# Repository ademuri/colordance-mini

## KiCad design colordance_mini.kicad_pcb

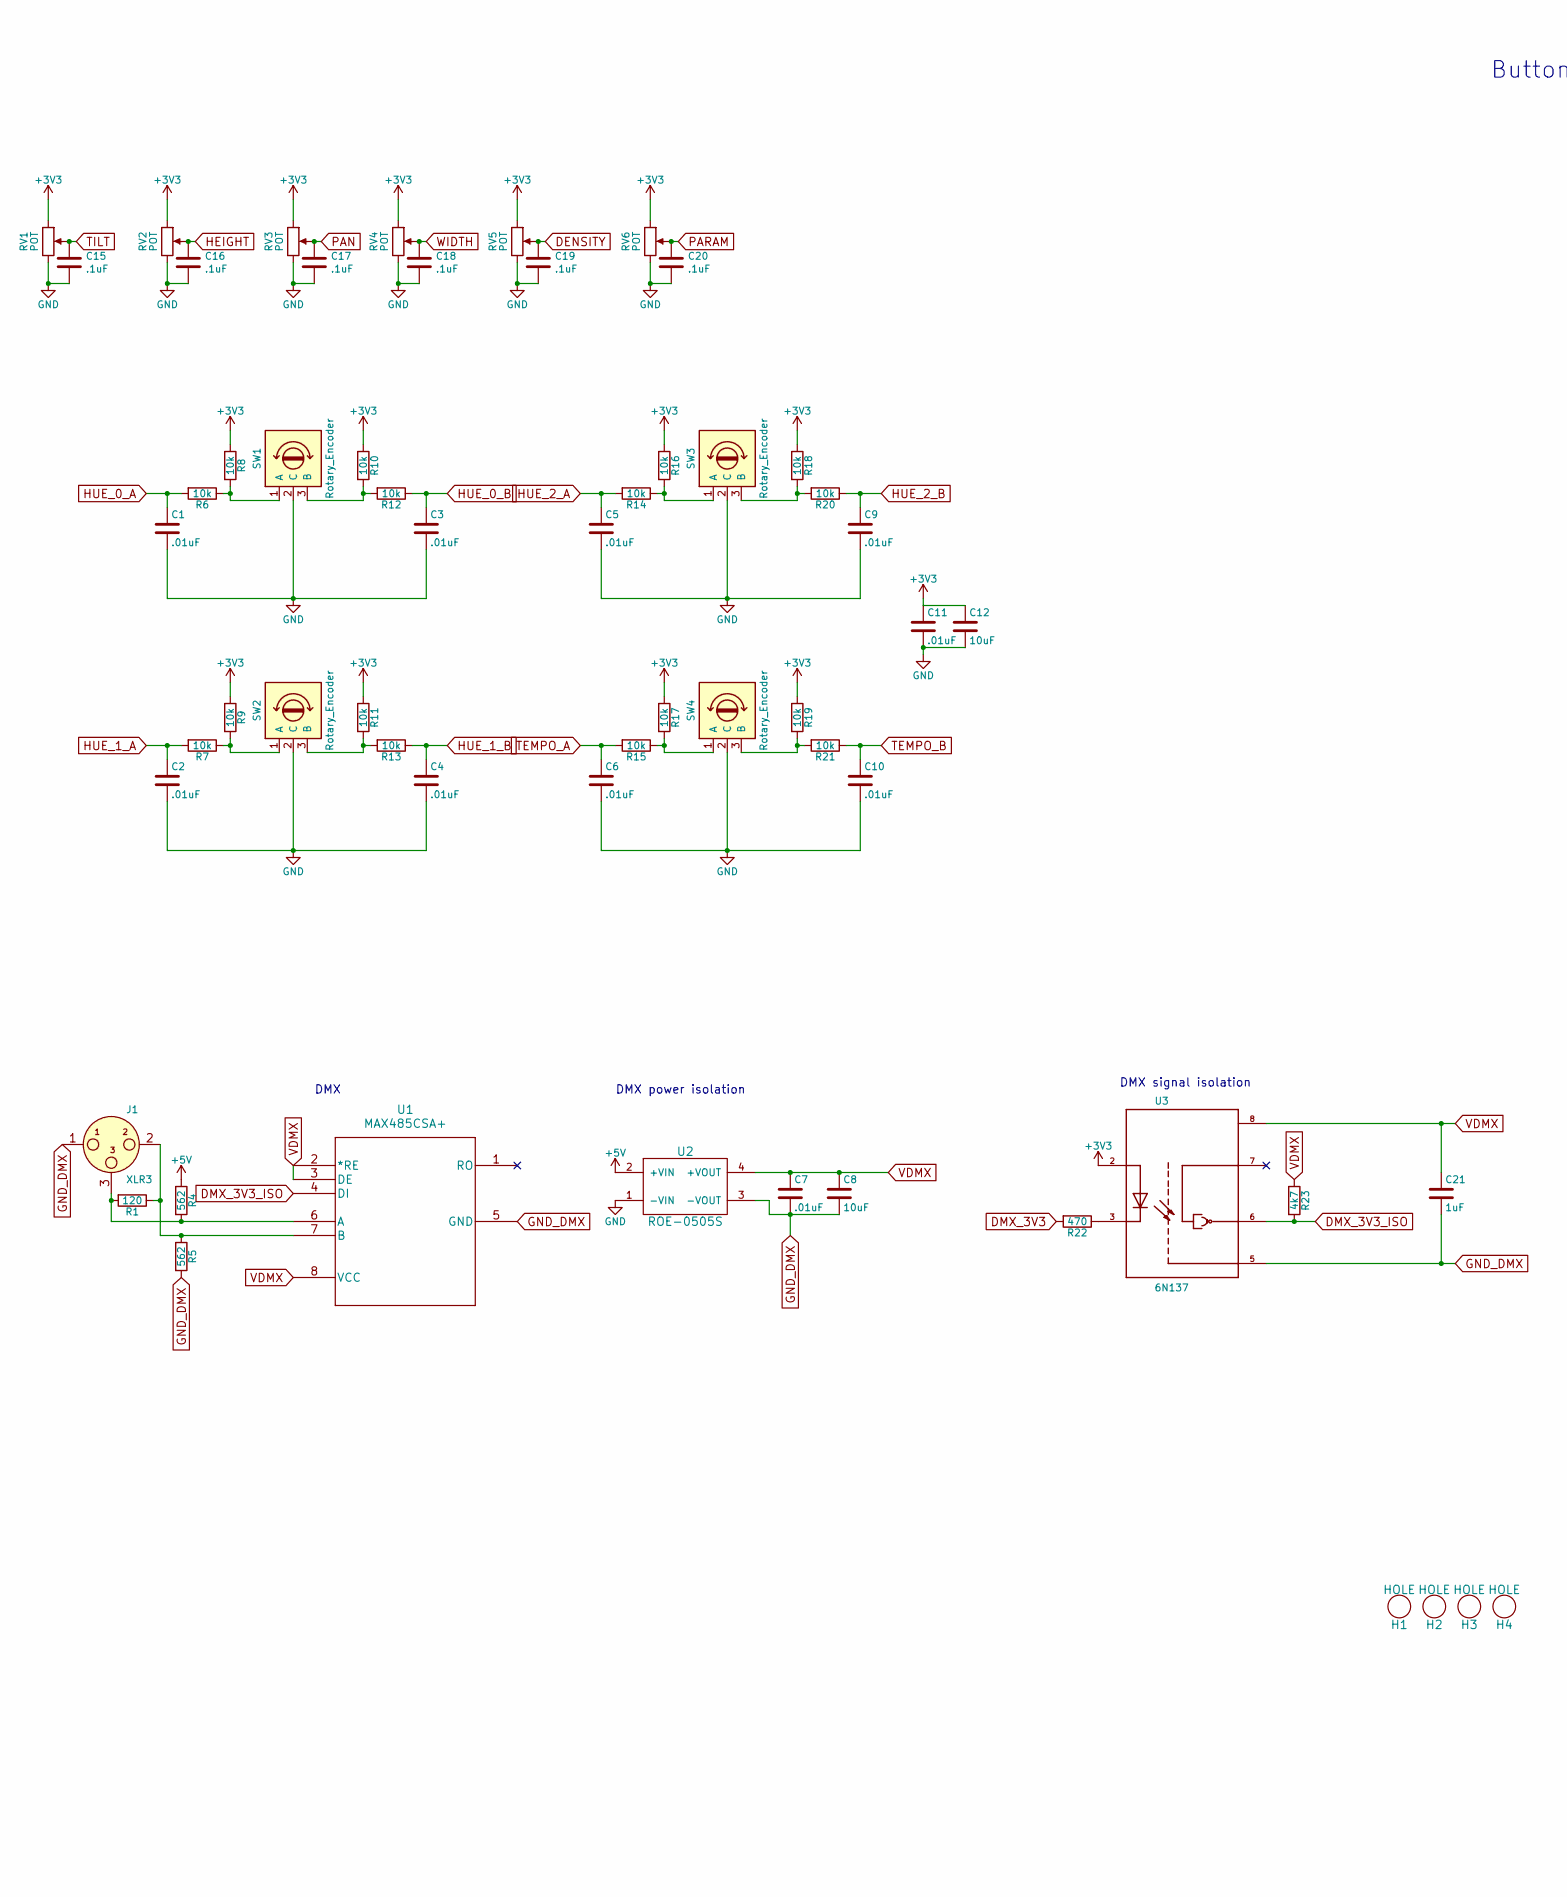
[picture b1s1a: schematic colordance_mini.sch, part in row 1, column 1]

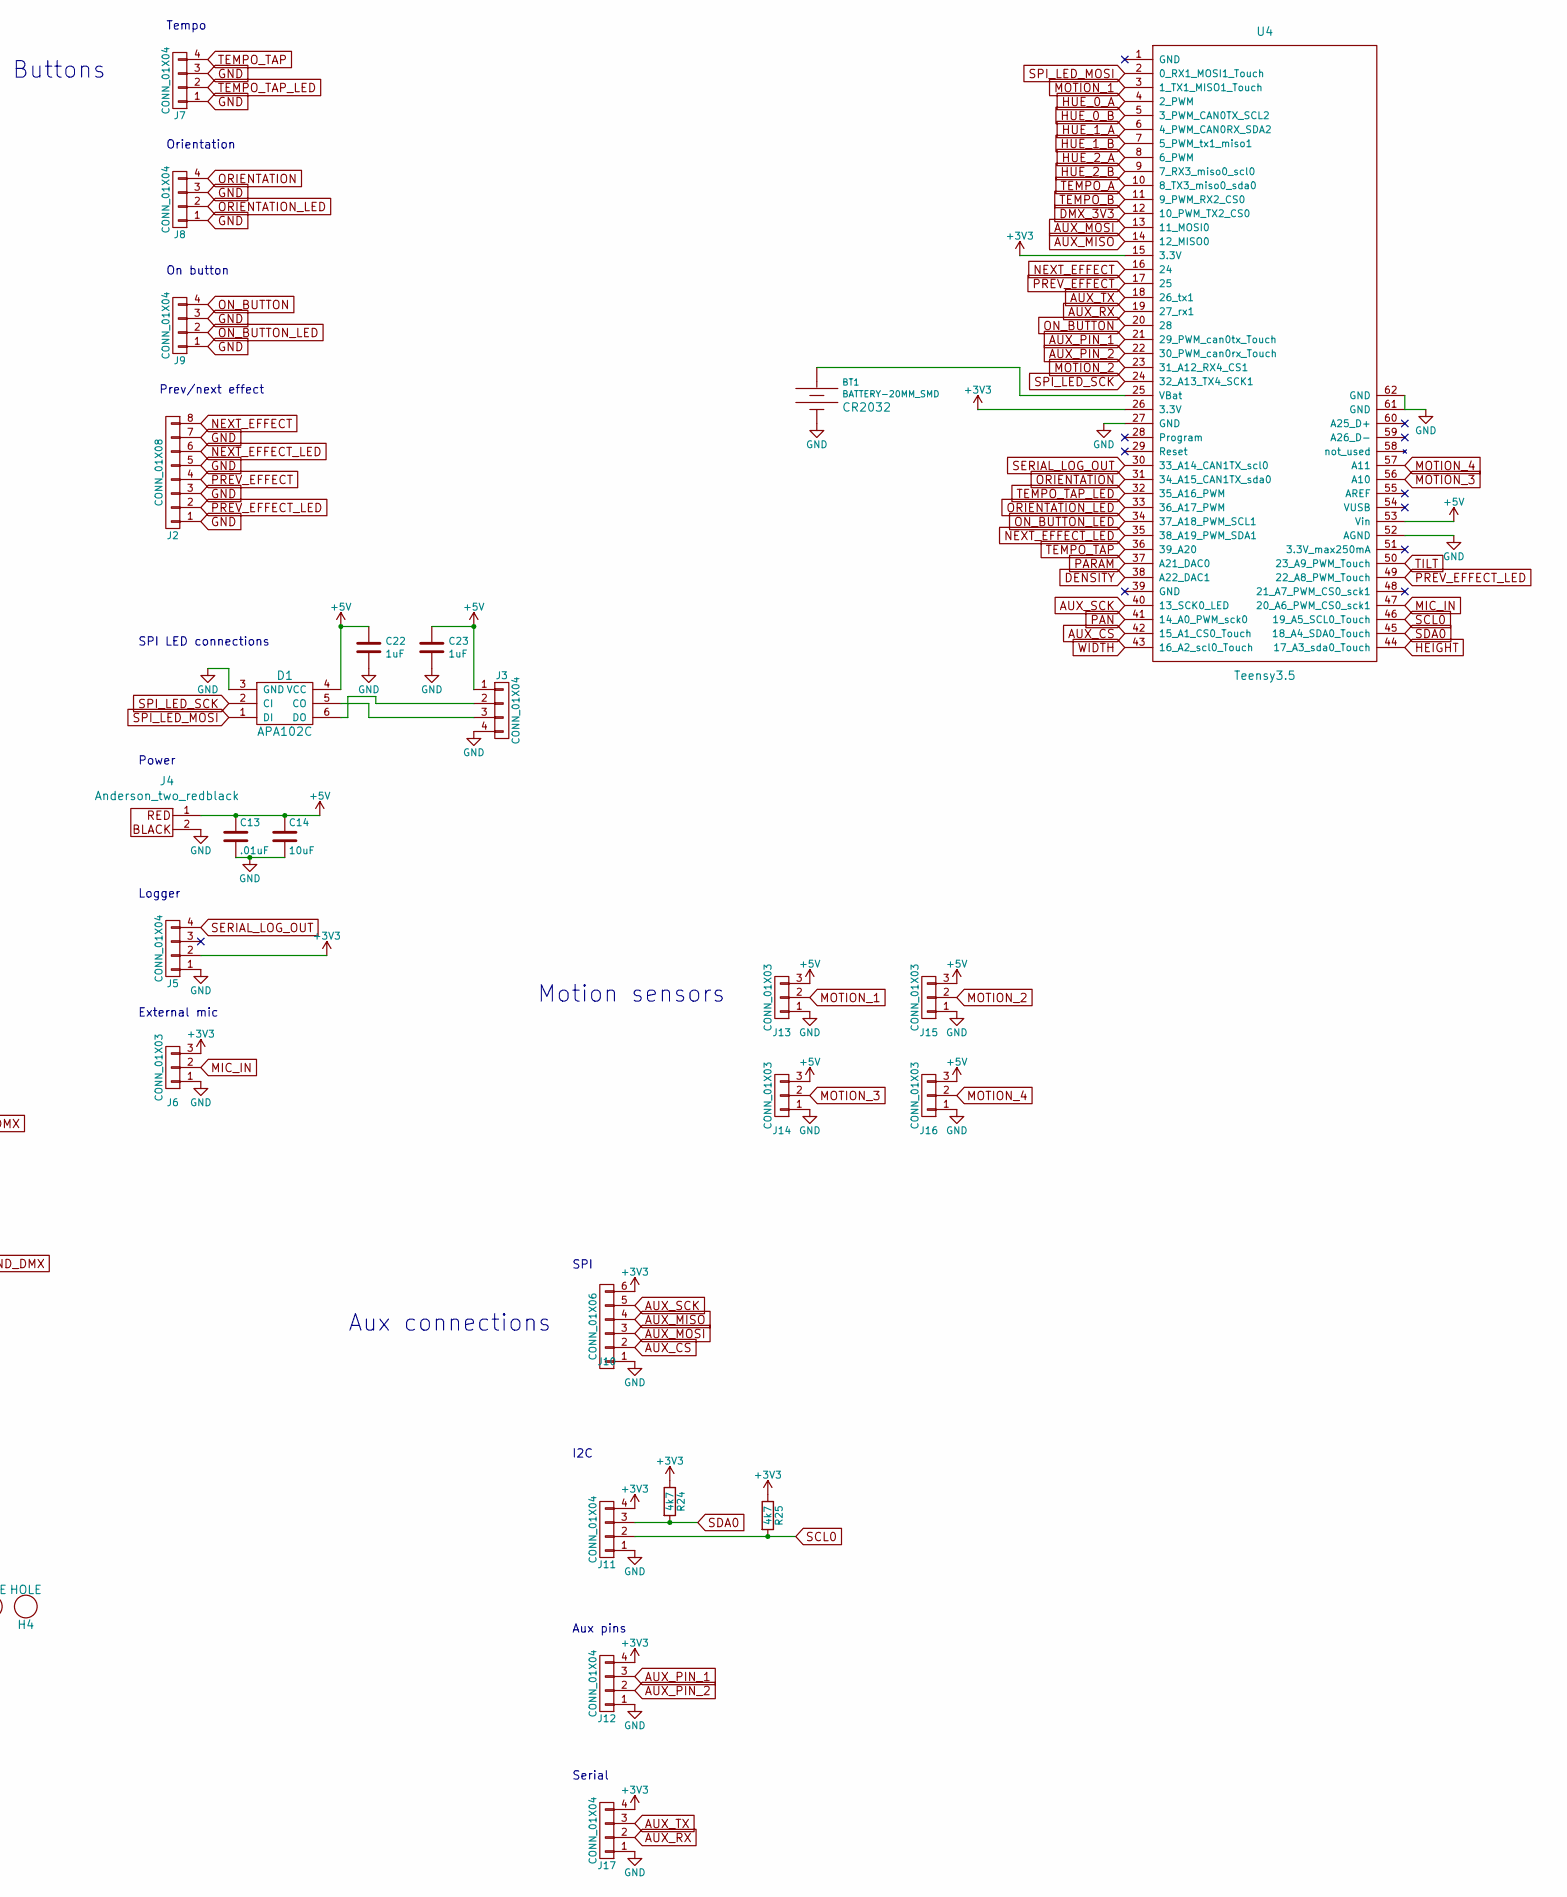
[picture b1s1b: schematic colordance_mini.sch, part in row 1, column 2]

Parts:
BT1: BATTERY-20MM_SMD; BATTCON_20MM
C1, C2, C3, C4, C5, C6, C7, C9, C10, C11, C13: .01uF; C_0603_HandSoldering
C8, C12, C14: 10uF; C_0603_HandSoldering
C15, C16, C17, C18, C19, C20: .1uF; C_0603_1608Metric_Pad1.05x0.95mm_HandSolder
C21, C22, C23: 1uF; C_0603_1608Metric_Pad1.05x0.95mm_HandSolder
D1: APA102C
H1, H2, H3, H4: HOLE; HOLE_M4
J1: XLR3; NC3FAH
J2: CONN_01X08; 1985250_phoenix_8pos_3.5mm
J3: CONN_01X04; PinHeader_1x04_P2.54mm_Vertical
J4: Anderson_two_redblack; Anderson_1337G3_straight_two
J5, J11, J12, J17: CONN_01X04; Pin_Header_Straight_1x04_Pitch2.54mm
J6, J13, J14, J15, J16: CONN_01X03; Pin_Header_Straight_1x03_Pitch2.54mm
J7, J8, J9: CONN_01X04; 1985218_phoenix_4pos_3.5mm
J10: CONN_01X06; Pin_Header_Straight_1x06_Pitch2.54mm
R1: 120; R_0603_HandSoldering
R4, R5: 562; R_0603_HandSoldering
R6, R7, R8, R9, R10, R11, R12, R13, R14, R15, R16, R17, R18, R19, R20, R21: 10k; R_0603_HandSoldering
R22: 470; R_0603_HandSoldering
R23, R24, R25: 4k7; R_0603_HandSoldering
RV1, RV2, RV3, RV4, RV5, RV6: POT; BOURNS_SLIDE_POT_45MM
SW1, SW2, SW3, SW4: Rotary_Encoder; BOURNS_PEC11R_ENCODER
U1: MAX485CSA+; SOIC-8-N
U2: ROE-0505S
U3: 6N137; DIP762W50P254L977H451Q8
U4: Teensy3.5; Teensy35_36

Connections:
+3V3: C11.1, C12.1, J5.2, J6.3, J10.6, J11.4, J12.4, J17.4, R8.1, R9.1, R10.1, R11.1, R16.1, R17.1, R18.1, R19.1, R24.1, R25.1, RV1.1, RV2.1, RV3.1, RV4.1, RV5.1, RV6.1, U3.2 (A), U4.15 (3.3V), U4.26 (3.3V)
+5V: C13.1, C14.1, C22.1, C23.1, D1.4 (VCC), J3.1, J4.1, J13.3, J14.3, J15.3, J16.3, R4.1, U2.2 (+VIN), U4.53 (Vin)
AUX_CS: J10.2, U4.42 (15_A1_CS0_Touch)
AUX_MISO: J10.4, U4.14 (12_MISO0)
AUX_MOSI: J10.3, U4.13 (11_MOSI0)
AUX_PIN_1: J12.3, U4.21 (29_PWM_can0tx_Touch)
AUX_PIN_2: J12.2, U4.22 (30_PWM_can0rx_Touch)
AUX_RX: J17.2, U4.19 (27_rx1)
AUX_SCK: J10.5, U4.40 (13_SCK0_LED)
AUX_TX: J17.3, U4.18 (26_tx1)
DENSITY: C19.1, RV5.2, U4.38 (A22_DAC1)
DMX_3V3: R22.2, U4.12 (10_PWM_TX2_CS0)
DMX_3V3_ISO: R23.2, U1.4 (DI), U3.6 (VO)
GND: BT1.2 (-), C1.2, C2.2, C3.2, C4.2, C5.2, C6.2, C9.2, C10.2, C11.2, C12.2, C13.2, C14.2, C15.2, C16.2, C17.2, C18.2, C19.2, C20.2, C22.2, C23.2, D1.3 (GND), J2.1, J2.3, J2.5, J2.7, J3.4, J4.2, J5.1, J6.1, J7.1, J7.3, J8.1, J8.3, J9.1, J9.3, J10.1, J11.1, J12.1, J13.1, J14.1, J15.1, J16.1, J17.1, RV1.3, RV2.3, RV3.3, RV4.3, RV5.3, RV6.3, SW1.2 (C), SW2.2 (C), SW3.2 (C), SW4.2 (C), U2.1 (-VIN), U4.27 (GND), U4.52 (AGND), U4.61 (GND), U4.62 (GND)
GND_DMX: C7.2, C8.2, C21.2, J1.1, R5.2, U1.5 (GND), U2.3 (-VOUT), U3.5 (GND)
HEIGHT: C16.1, RV2.2, U4.44 (17_A3_sda0_Touch)
HUE_0_A: C1.1, R6.2, U4.4 (2_PWM)
HUE_0_B: C3.1, R12.1, U4.5 (3_PWM_CAN0TX_SCL2)
HUE_1_A: C2.1, R7.2, U4.6 (4_PWM_CAN0RX_SDA2)
HUE_1_B: C4.1, R13.1, U4.7 (5_PWM_tx1_miso1)
HUE_2_A: C5.1, R14.2, U4.8 (6_PWM)
HUE_2_B: C9.1, R20.1, U4.9 (7_RX3_miso0_scl0)
MIC_IN: J6.2, U4.47 (20_A6_PWM_CS0_sck1)
MOTION_1: J13.2, U4.3 (1_TX1_MISO1_Touch)
MOTION_2: J15.2, U4.23 (31_A12_RX4_CS1)
MOTION_3: J14.2, U4.56 (A10)
MOTION_4: J16.2, U4.57 (A11)
NEXT_EFFECT: J2.8, U4.16 (24)
NEXT_EFFECT_LED: J2.6, U4.35 (38_A19_PWM_SDA1)
unnamed: BT1.1 (+), U4.25 (VBat)
unnamed: D1.5 (CO), J3.3
unnamed: D1.6 (DO), J3.2
unnamed: J1.2, R1.1, R5.1, U1.7 (B)
unnamed: J1.3, R1.2, R4.2, U1.6 (A)
unnamed: R6.1, R8.2, SW1.1 (A)
unnamed: R7.1, R9.2, SW2.1 (A)
unnamed: R10.2, R12.2, SW1.3 (B)
unnamed: R11.2, R13.2, SW2.3 (B)
unnamed: R14.1, R16.2, SW3.1 (A)
unnamed: R15.1, R17.2, SW4.1 (A)
unnamed: R18.2, R20.2, SW3.3 (B)
unnamed: R19.2, R21.2, SW4.3 (B)
unnamed: R22.1, U3.3 (C)
ON_BUTTON: J9.4, U4.20 (28)
ON_BUTTON_LED: J9.2, U4.34 (37_A18_PWM_SCL1)
ORIENTATION: J8.4, U4.31 (34_A15_CAN1TX_sda0)
ORIENTATION_LED: J8.2, U4.33 (36_A17_PWM)
PAN: C17.1, RV3.2, U4.41 (14_A0_PWM_sck0)
PARAM: C20.1, RV6.2, U4.37 (A21_DAC0)
PREV_EFFECT: J2.4, U4.17 (25)
PREV_EFFECT_LED: J2.2, U4.49 (22_A8_PWM_Touch)
SCL0: J11.2, R25.2, U4.46 (19_A5_SCL0_Touch)
SDA0: J11.3, R24.2, U4.45 (18_A4_SDA0_Touch)
SERIAL_LOG_OUT: J5.4, U4.30 (33_A14_CAN1TX_scl0)
SPI_LED_MOSI: D1.1 (DI), U4.2 (0_RX1_MOSI1_Touch)
SPI_LED_SCK: D1.2 (CI), U4.24 (32_A13_TX4_SCK1)
TEMPO_A: C6.1, R15.2, U4.10 (8_TX3_miso0_sda0)
TEMPO_B: C10.1, R21.1, U4.11 (9_PWM_RX2_CS0)
TEMPO_TAP: J7.4, U4.36 (39_A20)
TEMPO_TAP_LED: J7.2, U4.32 (35_A16_PWM)
TILT: C15.1, RV1.2, U4.50 (23_A9_PWM_Touch)
VDMX: C7.1, C8.1, C21.1, R23.1, U1.2 (*RE), U1.3 (DE), U1.8 (VCC), U2.4 (+VOUT), U3.8 (VCC)
WIDTH: C18.1, RV4.2, U4.43 (16_A2_scl0_Touch)

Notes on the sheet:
DMX
DMX power isolation
DMX signal isolation
Buttons
Tempo
Orientation
On button
Prev/next effect
SPI LED connections
Power
Motion sensors
Logger
External mic
SPI
Aux connections
I2C
Aux pins
Serial

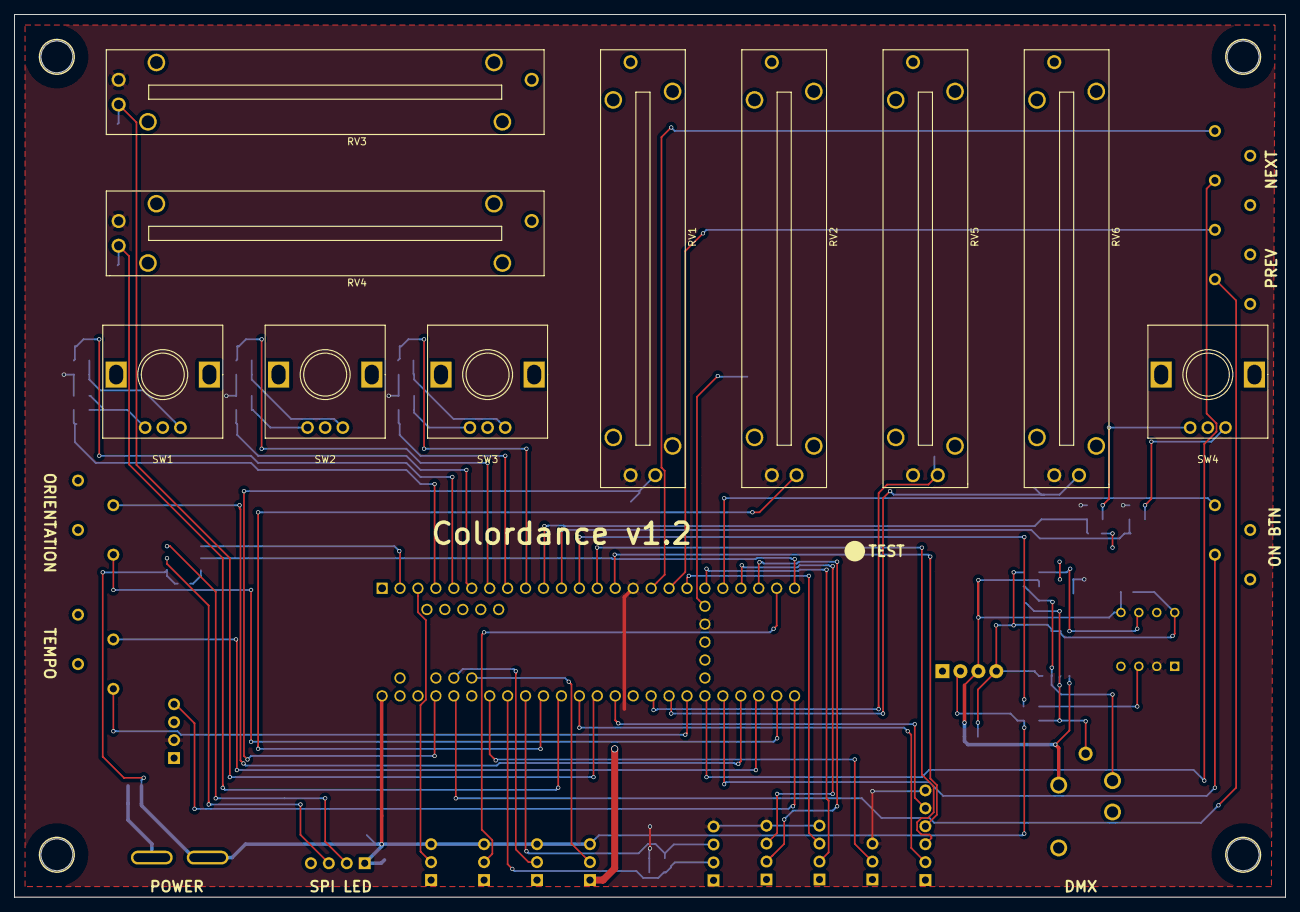
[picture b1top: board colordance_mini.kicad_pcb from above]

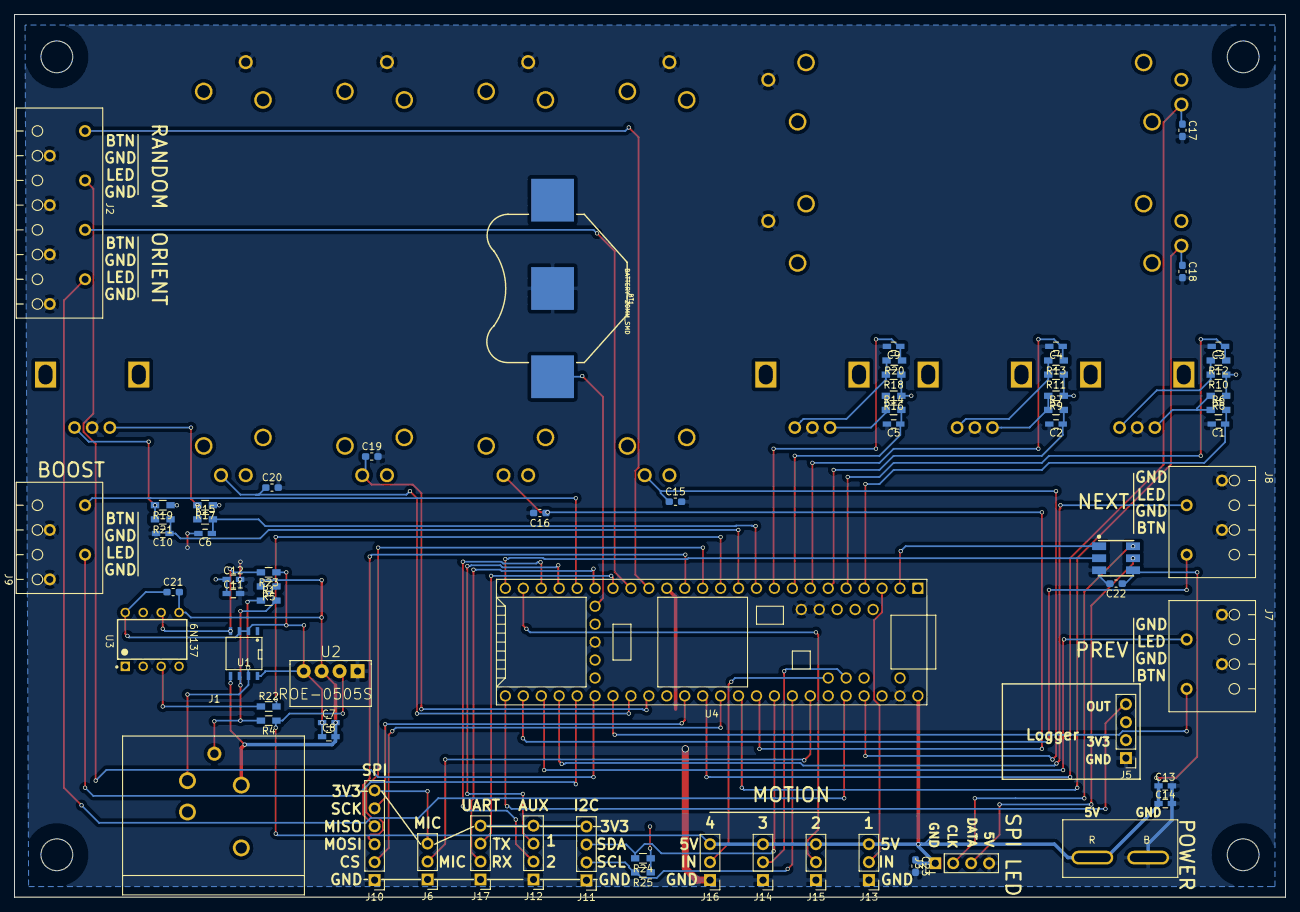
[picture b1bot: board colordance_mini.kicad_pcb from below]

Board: 2 copper layers, 180.0 x 125.0 mm, 83 parts (69 on the bottom side), 63 nets.

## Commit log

2017-11-24 Create a schematic
2017-11-24 Create the PCB. This is rev v1.0, I requested 5 boards from EasyEDA. As-yet untested.
2017-11-26 Update gerbers with missing layers
2017-11-26 Add front panel SVG v1.0
2018-03-24 Re-add cache
    This makes going between computers easier, since the used components
    will be in the cache.
2018-03-31 Add a teensy and a whole bunch of actuators for v1.1.
    Layout not yet updated.
2018-04-01 Add an onboard APA102 LED
2018-04-01 Associate footprints
2018-04-02 Rough placement
2018-04-02 Add mounting holes
2018-04-03 Placement finished
2018-04-03 Routing finished
2018-04-03 Silkscreen
2018-04-03 Fix holes and generate gerbers
2018-04-08 Add schematic and assembly sheet
2018-04-08 Add a test sketch for the DMX interface
2018-04-08 Add test sketches for the button and SPI LED
2018-04-14 Revision 1.1
    - Fix Teensy footprint to not use pads
    - Opto isolator gets 3v3 instead of 5v
    - Separate ground for DMX side
    - Fix DMX connector pinout
2018-05-02 Add more test code
2019-07-06 More test changes
2019-07-06 Unknown hardware changes
2019-07-06 Hardware revision v1.2:
    - Switch power to Anderson connector
    - Switch SPI LED connector to soldered 4-pin JST
    - Add filter caps to the pots
    - Add a few decoupling caps
2019-07-18 Update documentation
